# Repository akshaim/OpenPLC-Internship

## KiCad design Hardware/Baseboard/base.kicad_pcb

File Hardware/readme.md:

OpenPLC Hardware

The PLC has 2 boards- A. Baseboard B.Topboard

A. Baseboard
It consists of various electronics components.
They are-

1. Optocoupler PC817-
   Specifications- 1. Absolute Maximum Ratings-
		      Vce= 80V , Ic=50 mA
                   2. Input Output Isolation voltage= 5kV (rms)
		   3. CTR= 50 % at If=5mA and Vce=5V
		   4. Package= 4 pin DIP

2. Darlington transistor array ULN2803-
   Specifications- 1. Absolute Maximum Ratings-
   		      Vo=50V , Vi=30V ,Ic=500mA
                   2. It has 8 npn darlington pair
		   3. Package= 18 pin DIP

3. Zener Diodes-
   Specifications- 1. Vz= 5.1 V
                   2. Power= 200mW
                   3. Package= SMD MiniMelf Handsoldering

4. Relay JQC-3FF-S-Z
   Specifications- 1. Nominal coil voltage DC= 5V DC
                   2. Output Current- 5V DC,1A
                   3. Type- SPDT relay

5. Pi Zero Breakout-
   1. 2*20=40 pin female socket                  

6. Analog Breakout-
   1. 4 pin female socket

7. Buck Converter LM2596-
   Specifications- 1. Absolute Maximum Ratings-
		      Vin=40V , Io=3A
                   2. 24V-5V Buck Converter-
                      4.75V <= Vin <= 40V
                      200mA <= Il <= 3A
                   3. Package- TO-263
8. LDO AMS117-3.3V
   Specifications- 1. Absolute Maximum Ratings-
                      Vin=15V
                   2. 5V-3.3V LDO
                      Vin>= 4.85V
                   3. Dropout Voltage= 1.3V
                   4. Package- SOT-223

9. Resistors-
   Specifications- 1. Value= 10K Power Wattage= 0.250W
                   2. Package- SMD 0603 Hand solderable.
                   3. Value= 5K Power Wattage= 0.250W
                   4. Package- SMD 0603 Hand solderable.

10. Capacitors-
    Specifications- 1. Value= 100nF,ceramic Working Voltage>5V
                    2. Value= 22uF,tantalum Working Volatge>5V

11. Screw terminals- 1. 12 pin
                     2. Current-1-5A

B.Topboard-
1. Raspberry Pi zero-
   Specifications- 1. Processor - single core 1 GHz ARM processor
                   2. RAM- 512 MB
                   3. 40 pin GPIO Header

2. Analog to Digital Converter ADS1018
   Specifications- 1.Vin= 2-5.5V
                   2. Current Consumption= 150uA
                   3. 12 bit ADC
                   4. Internal Oscillator

3. Resistors-
   Specifications- 1. Value= 10K Power Wattage= 0.250W
                   2. Package- SMD 0603 Hand solderable.
                   3. Value= 5K Power Wattage= 0.250W
                   4. Package- SMD 0603 Hand solderable.

4. Capacitors-
   Specifications- 1. Value= 100nF,ceramic Working Voltage>5V

5. GPIO breakout- 1. 2*20=40 pin female socket 

6. Ethernet breakout- 1. 7 pin female socket

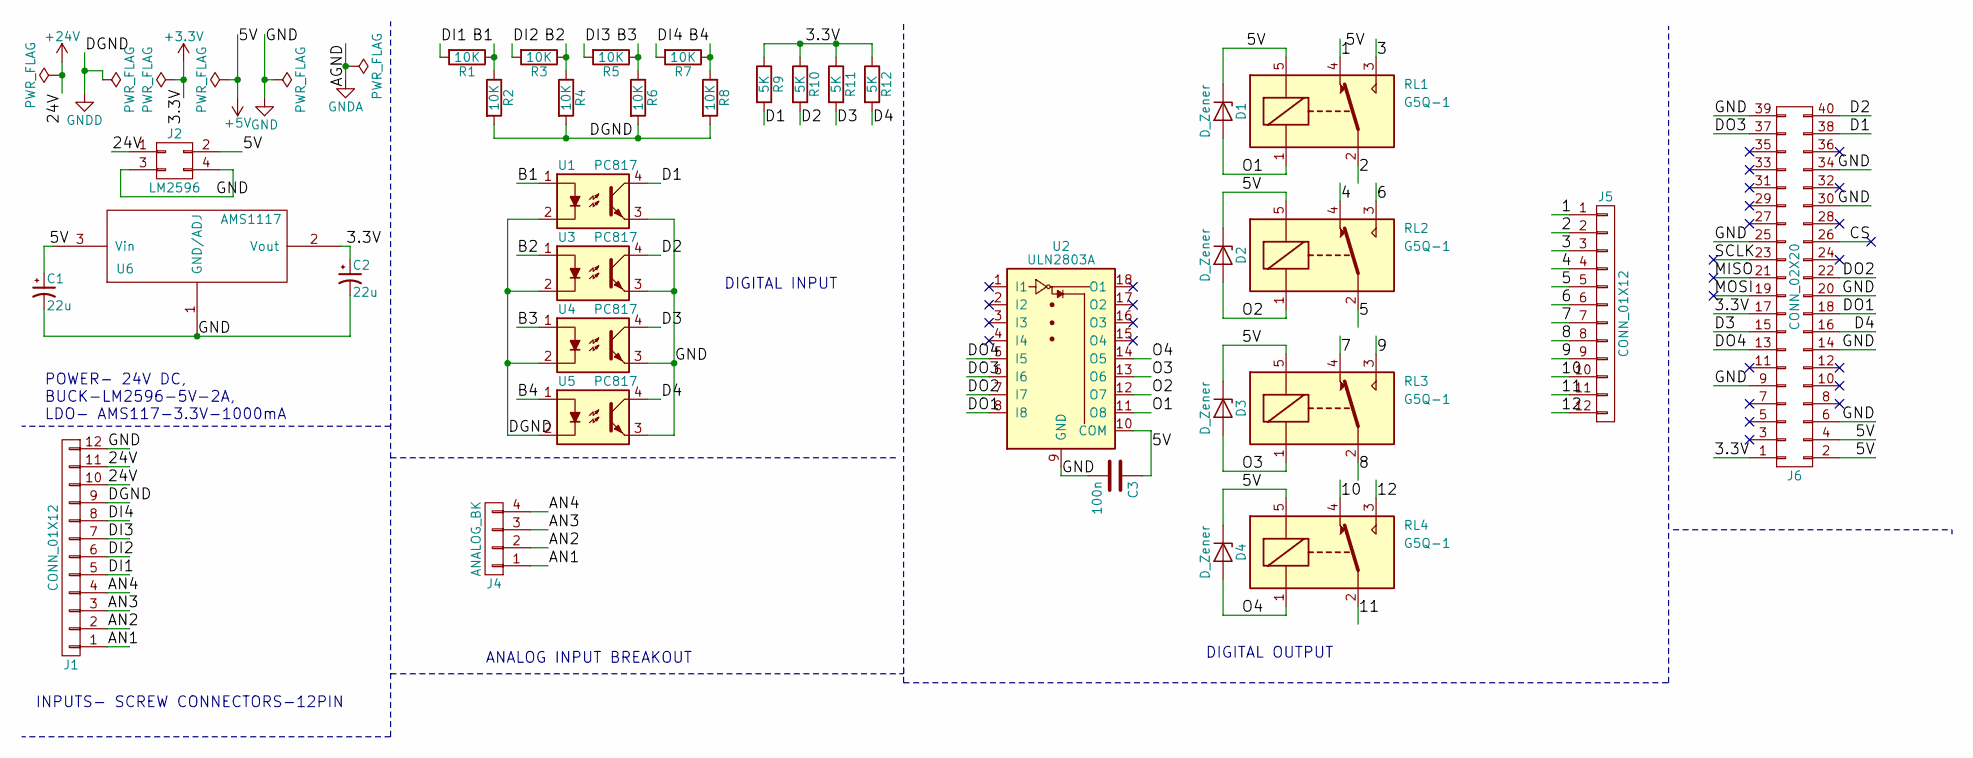
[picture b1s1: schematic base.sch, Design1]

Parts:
C1, C2: 22u; C_0603_HandSoldering
C3: 100n; C_0603_HandSoldering
D1, D2, D3, D4: D_Zener; D_MiniMELF_Handsoldering
J1, J5: CONN_01X12; TerminalBlock_Pheonix_MKDS1.5-12pol
J2: LM2596
J4: ANALOG_BK; Socket_Strip_Straight_1x04_Pitch2.54mm
J6: CONN_02X20; Socket_Strip_Straight_2x20_Pitch2.54mm
R1, R2, R3, R4, R5, R6, R7, R8: 10K; R_0603_HandSoldering
R9, R10, R11, R12: 5K; R_0603_HandSoldering
RL1, RL2, RL3, RL4: G5Q-1; Relay-JQC-3FF-5V
U1, U3, U4, U5: PC817; DIP-4_W7.62mm
U2: ULN2803A; DIP-18_W7.62mm
U6: AMS1117; SOT-223-3Lead_TabPin2

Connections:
+3V3: C2.1, J6.1, J6.17, R9.1, R10.1, R11.1, R12.1, U6.2 (Vout)
+5V: C1.1, C3.1, D1.1 (K), D2.1 (K), D3.1 (K), D4.1 (K), J2.2, J6.2, J6.4, RL1.5, RL2.5, RL3.5, RL4.5, U2.10 (COM), U6.3 (Vin)
+24V: J1.10, J1.11, J2.1
/1: J5.1, RL1.4
/2: J5.2, RL1.2
/3: J5.3, RL1.3
/4: J5.4, RL2.4
/5: J5.5, RL2.2
/6: J5.6, RL2.3
/7: J5.7, RL3.4
/8: J5.8, RL3.2
/9: J5.9, RL3.3
/10: J5.10, RL4.4
/11: J5.11, RL4.2
/12: J5.12, RL4.3
/AN1: J1.1, J4.1
/AN2: J1.2, J4.2
/AN3: J1.3, J4.3
/AN4: J1.4, J4.4
/B1: R1.1, R2.1, U1.1
/B2: R3.1, R4.1, U3.1
/B3: R5.1, R6.1, U4.1
/B4: R7.1, R8.1, U5.1
/CS: J6.26
/D1: J6.38, R9.2, U1.4
/D2: J6.40, R10.2, U3.4
/D3: J6.15, R11.2, U4.4
/D4: J6.16, R12.2, U5.4
/DI1: J1.5, R1.2
/DI2: J1.6, R3.2
/DI3: J1.7, R5.2
/DI4: J1.8, R7.2
/DO1: J6.18, U2.8 (I8)
/DO2: J6.22, U2.7 (I7)
/DO3: J6.37, U2.6 (I6)
/DO4: J6.13, U2.5 (I5)
/MISO: J6.21
/MOSI: J6.19
/O1: D1.2 (A), RL1.1, U2.11 (O8)
/O2: D2.2 (A), RL2.1, U2.12 (O7)
/O3: D3.2 (A), RL3.1, U2.13 (O6)
/O4: D4.2 (A), RL4.1, U2.14 (O5)
/SCLK: J6.23
GND: C1.2, C2.2, C3.2, J1.12, J2.3, J2.4, J6.6, J6.9, J6.14, J6.20, J6.25, J6.30, J6.34, J6.39, U1.3, U2.9 (GND), U3.3, U4.3, U5.3, U6.1 (GND/ADJ)
GNDD: J1.9, R2.2, R4.2, R6.2, R8.2, U1.2, U3.2, U4.2, U5.2

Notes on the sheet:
POWER- 24V DC, BUCK-LM2596-5V-2A, LDO- AMS117-3.3V-1000mA
INPUTS- SCREW CONNECTORS-12PIN
DIGITAL INPUT
ANALOG INPUT BREAKOUT
DIGITAL OUTPUT

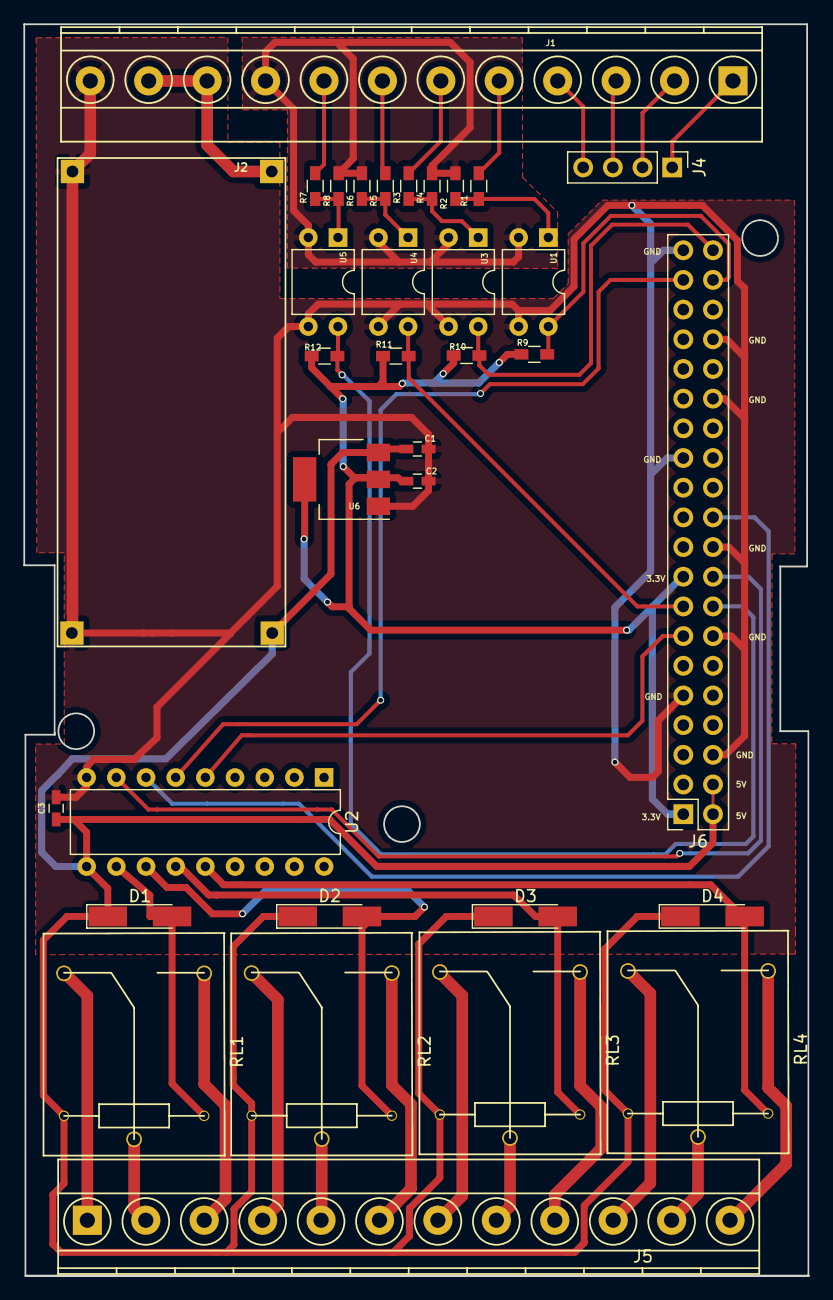
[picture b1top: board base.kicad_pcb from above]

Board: 2 copper layers, 67.2 x 107.1 mm, 34 parts (0 on the bottom side), 41 nets.

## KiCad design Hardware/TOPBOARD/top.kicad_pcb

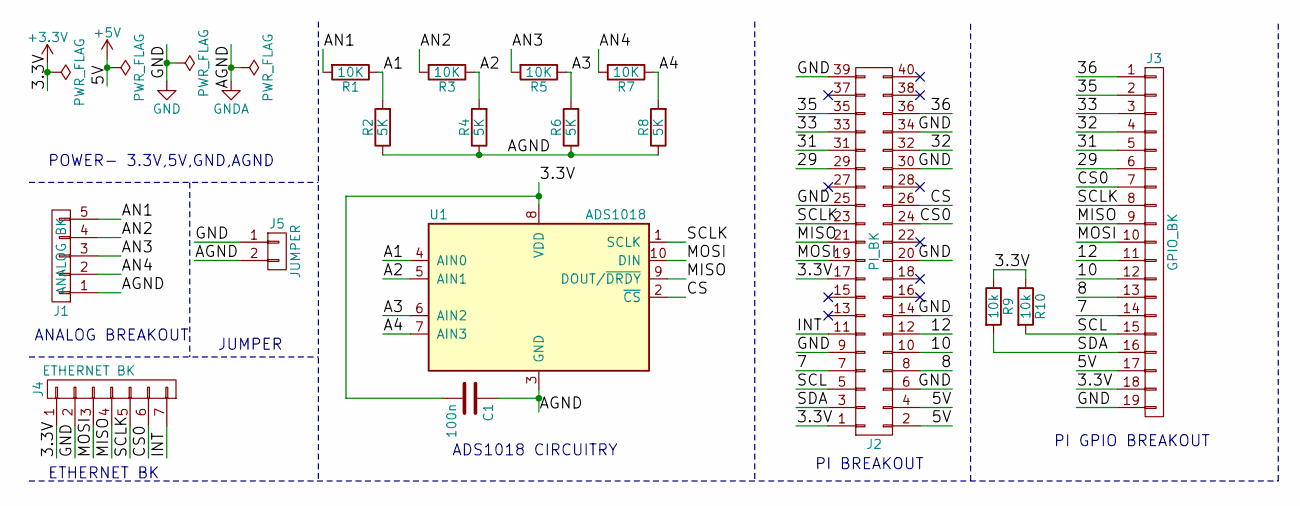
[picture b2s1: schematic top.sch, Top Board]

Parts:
C1: 100n; C_0603_HandSoldering
J1: ANALOG BK; Socket_Strip_Straight_1x05_Pitch2.00mm
J2: PI_BK; Socket_Strip_Straight_2x20_Pitch2.54mm
J3: GPIO_BK; Socket_Strip_Straight_1x19_Pitch2.54mm
J4: ETHERNET BK; Socket_Strip_Straight_1x07_Pitch2.54mm
J5: JUMPER; Pin_Header_Straight_1x02_Pitch2.00mm
R1, R3, R5, R7: 10K; R_0603_HandSoldering
R2, R4, R6, R8: 5K; R_0603_HandSoldering
R9, R10: 10k; R_0603_HandSoldering
U1: ADS1018

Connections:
+3V3: C1.2, J2.1, J2.17, J3.18, J4.1, R9.1, R10.1, U1.8 (VDD)
+5V: J2.2, J2.4, J3.17
/7: J2.7, J3.14
/8: J2.8, J3.13
/10: J2.10, J3.12
/12: J2.12, J3.11
/29: J2.29, J3.6
/31: J2.31, J3.5
/32: J2.32, J3.4
/33: J2.33, J3.3
/35: J2.35, J3.2
/36: J2.36, J3.1
/A1: R1.1, R2.2, U1.4 (AIN0)
/A2: R3.1, R4.2, U1.5 (AIN1)
/A3: R5.1, R6.2, U1.6 (AIN2)
/A4: R7.1, R8.2, U1.7 (AIN3)
/AN1: J1.5, R1.2
/AN2: J1.4, R3.2
/AN3: J1.3, R5.2
/AN4: J1.2, R7.2
/CS: J2.26, U1.2 (~CS)
/CS0: J2.24, J3.7, J4.6
/INT: J2.11, J4.7
/MISO: J2.21, J3.9, J4.4, U1.9 (DOUT/~DRDY)
/MOSI: J2.19, J3.10, J4.3, U1.10 (DIN)
/SCL: J2.5, J3.15, R10.2
/SCLK: J2.23, J3.8, J4.5, U1.1 (SCLK)
/SDA: J2.3, J3.16, R9.2
GND: J2.6, J2.9, J2.14, J2.20, J2.25, J2.30, J2.34, J2.39, J3.19, J4.2, J5.1
GNDA: C1.1, J1.1, J5.2, R2.1, R4.1, R6.1, R8.1, U1.3 (GND)

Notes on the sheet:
POWER- 3.3V,5V,GND,AGND
ANALOG BREAKOUT
ADS1018 CIRCUITRY
PI BREAKOUT
PI GPIO BREAKOUT
ETHERNET BK
JUMPER

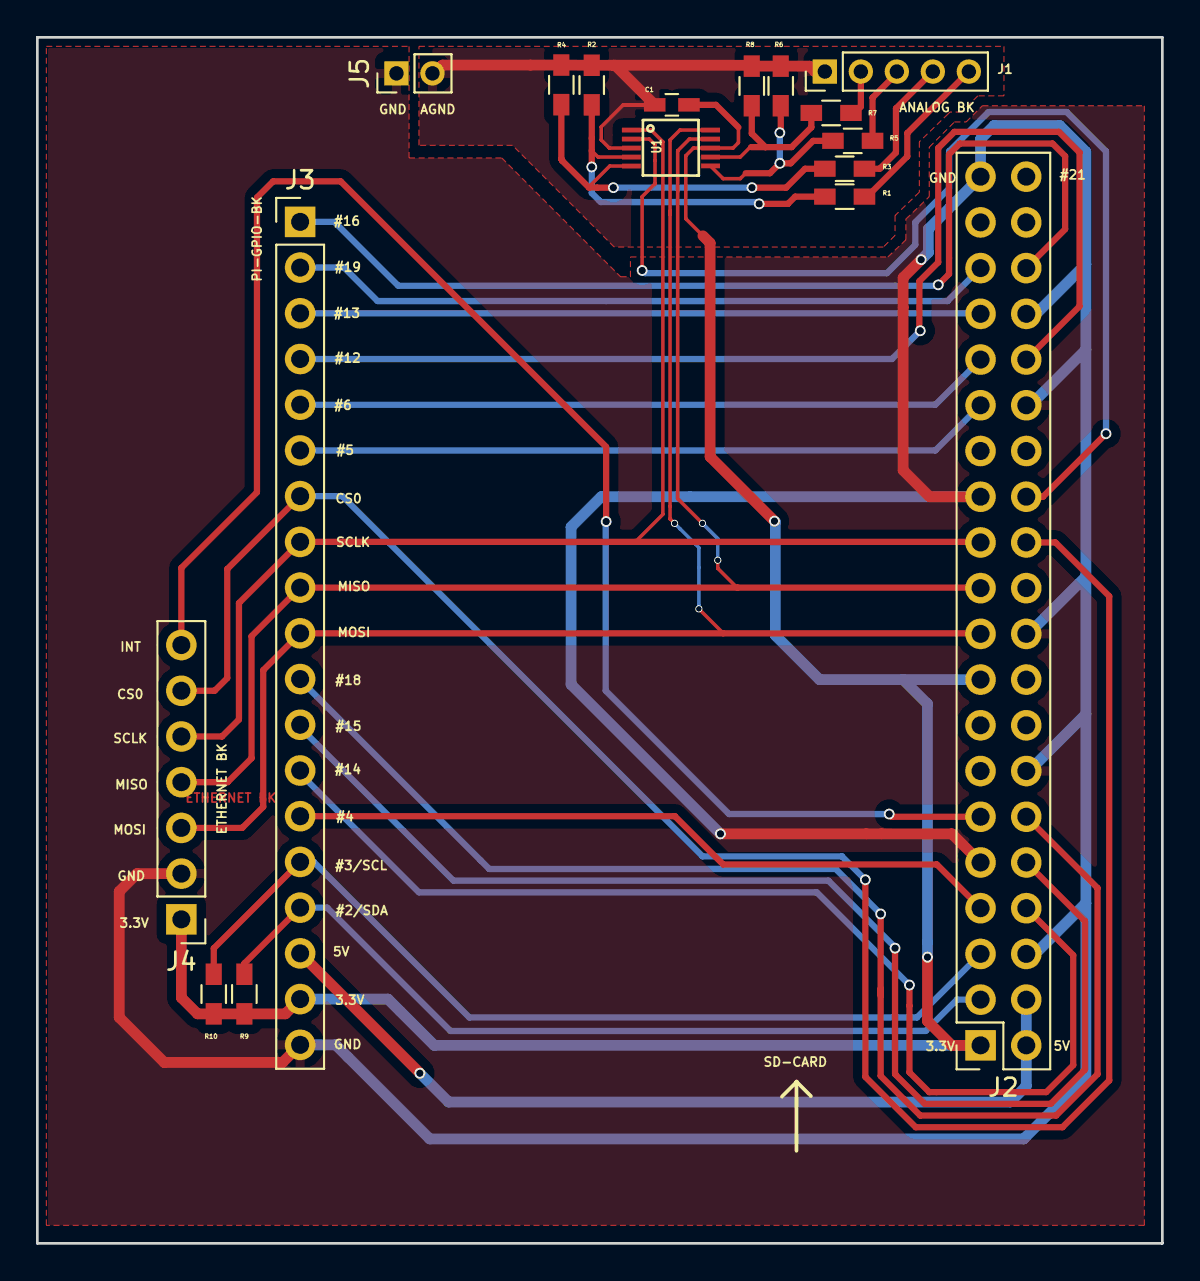
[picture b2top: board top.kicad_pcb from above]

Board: 2 copper layers, 62.5 x 67.0 mm, 17 parts (0 on the bottom side), 30 nets.

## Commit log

2017-05-15 Folder Structure and Readme
2017-05-16 speed controller
2017-05-19 elavator 1st commit
2017-05-23 event fb
2017-06-01 Scripts and Documentation for Captive Portal
2017-06-01 Scripts and Documentation for adding a Power Button
2017-06-02 functionalities of events and fbrt blocks
2017-06-05 KICAD FILES FOR BASEBOARD
2017-06-07 Scripts and Documentation for Power Button
2017-06-12 Finalised Kicad files
2017-06-13 Example apps for events and fbrt blocks added
2017-06-23 Modified error free baseboard file along with readme file
2017-07-04 Baseboard and topboard final files along with certain issues+scope.md which include subtle errors
2017-07-09 Scripts and Documentation for Headless AP mode and Captive Portal
2017-07-09 Linux Firmware Development Files
2017-07-09 Power Button
2017-07-09 Scripts and Documentation for adding Reset Button
2017-07-09 Scripts and Documentation for adding Power Button
2017-07-09 Scripts and Documentation for configuring PLC in headless mode and a captive portal
2017-07-09 Interfaces and Applications for ADXL345
2017-07-09 Steps for interfacing ENC28J60 Ethernet Module
2017-07-09 Linux- Drivers,C,C++,Bash Scripts, Config Files Documentation
2017-07-25 Untracked baseboard files
